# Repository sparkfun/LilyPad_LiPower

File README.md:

LilyPad LiPower
========================================

[*LilyPad LiPower (DEV-11260)*](https://www.sparkfun.com/products/11260)

Attach a single cell LiPo battery, flip the power switch, and you will have a 5V supply to power your LilyPad network. 
Good up to 150mA. Short circuit protected.
This board has a JST connector, which will connect to our JST terminated single cell 3.7V LiPo batteries. 

Repository Contents
-------------------

* **/Hardware** - Eagle design files (.brd, .sch)
* **/Production** - Production panel files (.brd)

Documentation
--------------
* **[SparkFun Fritzing repo](https://github.com/sparkfun/Fritzing_Parts)** - Fritzing diagrams for SparkFun products.
* **[SparkFun 3D Model repo](https://github.com/sparkfun/3D_Models)** - 3D models of SparkFun products. 

License Information
-------------------
This product is _**open source**_! 

The **hardware** is released under [Creative Commons ShareAlike 4.0 International](https://creativecommons.org/licenses/by-sa/4.0/).

Please use, reuse, and modify these files as you see fit. Please maintain attribution to SparkFun Electronics and release anything derivative under the same license.

Distributed as-is; no warranty is given.

- Your friends at SparkFun.

_**Note:** A portion of this sale is given back to Dr. Leah Buechley for continued development and education of e-textiles._

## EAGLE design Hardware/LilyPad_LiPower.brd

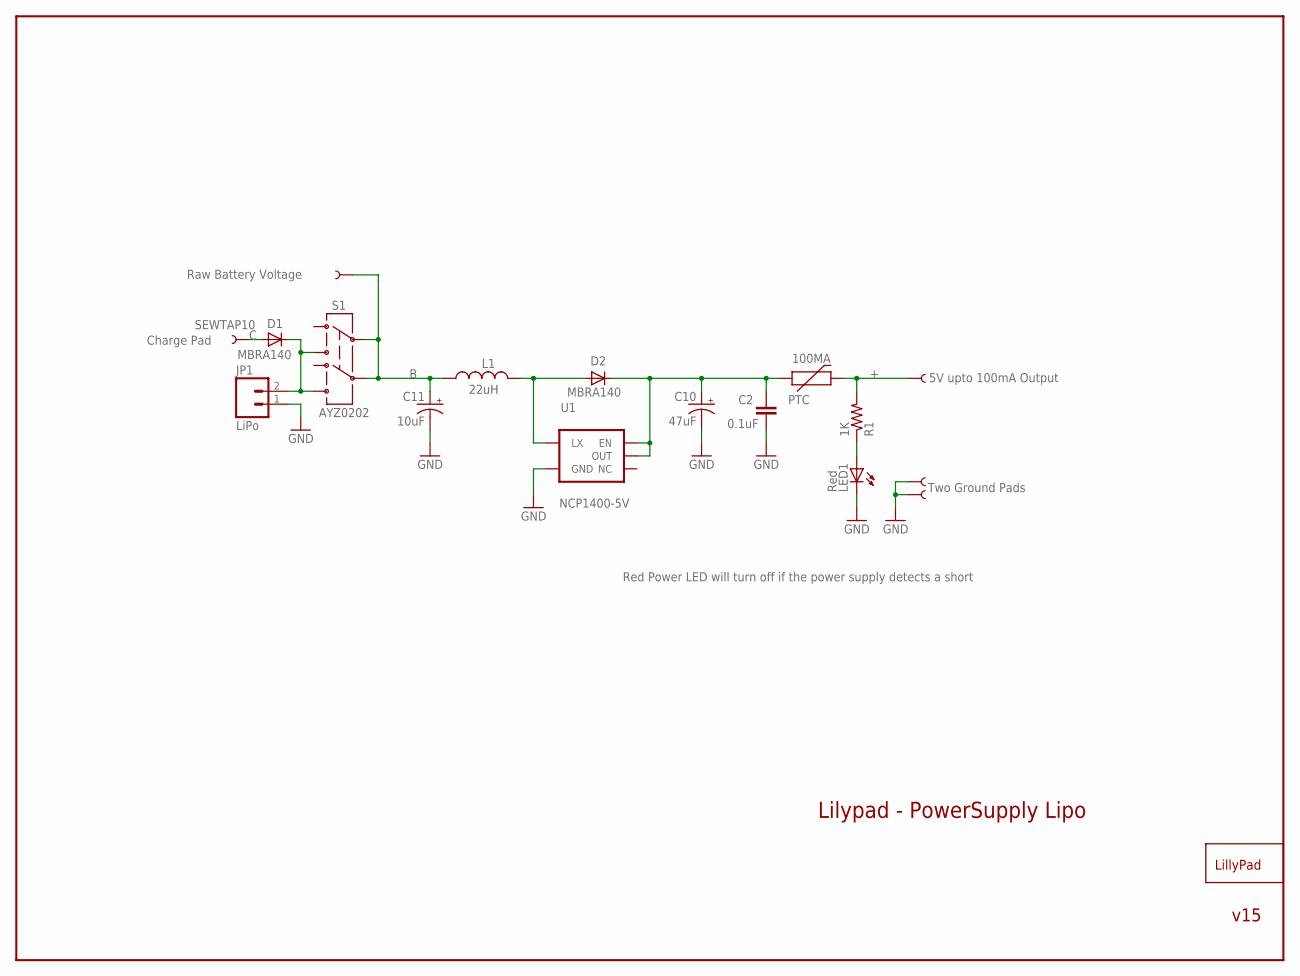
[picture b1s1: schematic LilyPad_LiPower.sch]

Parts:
100MA: PTC; PTC-1206
C2: 0.1uF; 0603-CAP
C10: 47uF; EIA3528-21
C11: 10uF; CPOL_1206
D1, D2: MBRA140; SMA-DIODE
JP1: LiPo; JST-2-SMD
L1: 22uH; CR54
LED1: Red; LED-1206
R1: 1K; 0603-RES
S1: AYZ0202
U1: NCP1400-5V; SOT23-5
U$1, U$2, U$3, U$4, U$5: SEWTAP10; PETAL-LONG-2-2SIDE
U$7: LOGO-LPLP; LOGO-LILYPAD

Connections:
+: 100MA.2, R1.2, U$1.1
B: C11.A (+), L1.P$2 (2), S1.2, S1.5, U$3.1
C: D1.A, U$2.1
GND: C2.2, C10.C (-), C11.C (-), JP1.1, LED1.C, U1.4 (GND), U$4.1, U$5.1
unnamed: LED1.A, R1.1
unnamed: 100MA.1, C2.1, C10.A (+), D2.C, U1.1 (EN), U1.2 (OUT)
unnamed: D1.C, JP1.2, S1.1 (3), S1.4 (6)
unnamed: D2.A, L1.P$1 (1), U1.5 (LX)

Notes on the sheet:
Lilypad - PowerSupply Lipo
Raw Battery Voltage
Charge Pad
5V upto 100mA Output
Two Ground Pads
Red Power LED will turn off if the power supply detects a short
v15

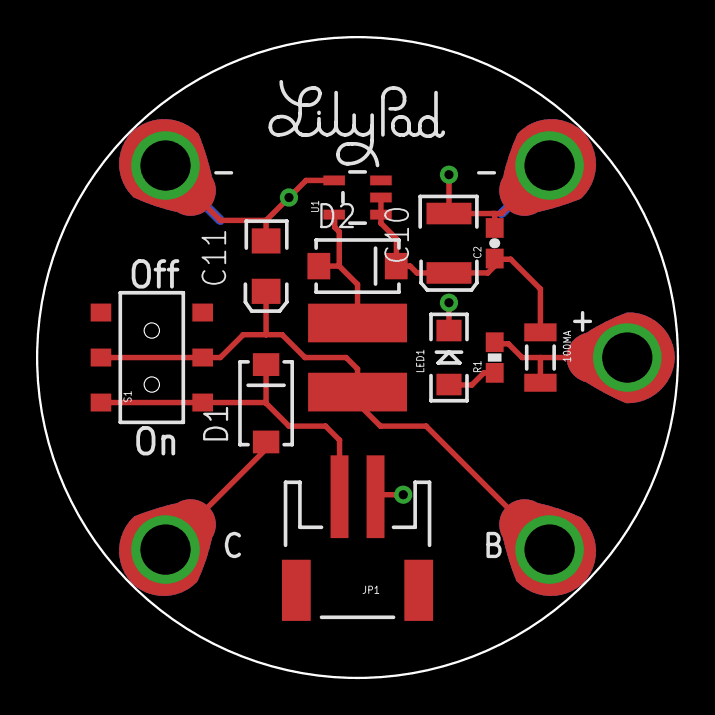
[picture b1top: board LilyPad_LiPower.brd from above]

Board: 2 copper layers, 35.6 x 35.6 mm, 18 parts (0 on the bottom side), 8 nets.

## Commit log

2015-05-06 Adding hardware files, updating README
